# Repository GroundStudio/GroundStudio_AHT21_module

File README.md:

GroundStudio AHT21 module
====================================

Get it from [ardushop.ro](https://ardushop.ro/ro/home/2510-modul-senzor-umiditate-si-temperatura-aht21-groundstudio.html)

Explore all the GroundStudio products at [GroundStudio.ro](https://groundstudio.ro/)

Description
-------------------
Temperature and humidity sensor module based on AHT21 chip.

Contents
-------------------

* [/Documentation](https://github.com/GroundStudio/GroundStudio_AHT21_module/tree/main/Documentation) -- Contains documentation written during creation of this repository, with readme.md index of its own!
* [/Firmware](https://github.com/GroundStudio/GroundStudio_AHT21_module/tree/main/Firmware) -- Firmware (bootloaders, etc)
* [/Hardware](https://github.com/GroundStudio/GroundStudio_AHT21_module/tree/main/Hardware) -- Schematics, layout.
* [/Libraries](https://github.com/GroundStudio/GroundStudio_AHT21_module/tree/main/Libraries) -- Arduino/CircuitPython libraries. 
* [/Tools](https://github.com/GroundStudio/GroundStudio_AHT21_module/tree/main) -- Tools needed for compiling, uploading bootloader, etc.

Versions
-------------------
*(Not all tags shown)*
* [V0.0.1] Initial version

License
-------------------

This is released under the [Attribution-ShareAlike 4.0 International (CC BY-SA 4.0)](https://creativecommons.org/licenses/by-sa/4.0/) license. 
**You are welcome to use this for commercial purposes.**

Please consider contributing back to this project or others to help the open-source hardware community continue to thrive and grow! 

Certifications:

[Open Source Hardware Association](https://certification.oshwa.org/ro000019.html)   
   
[
](https://certification.oshwa.org/ro000019.html)

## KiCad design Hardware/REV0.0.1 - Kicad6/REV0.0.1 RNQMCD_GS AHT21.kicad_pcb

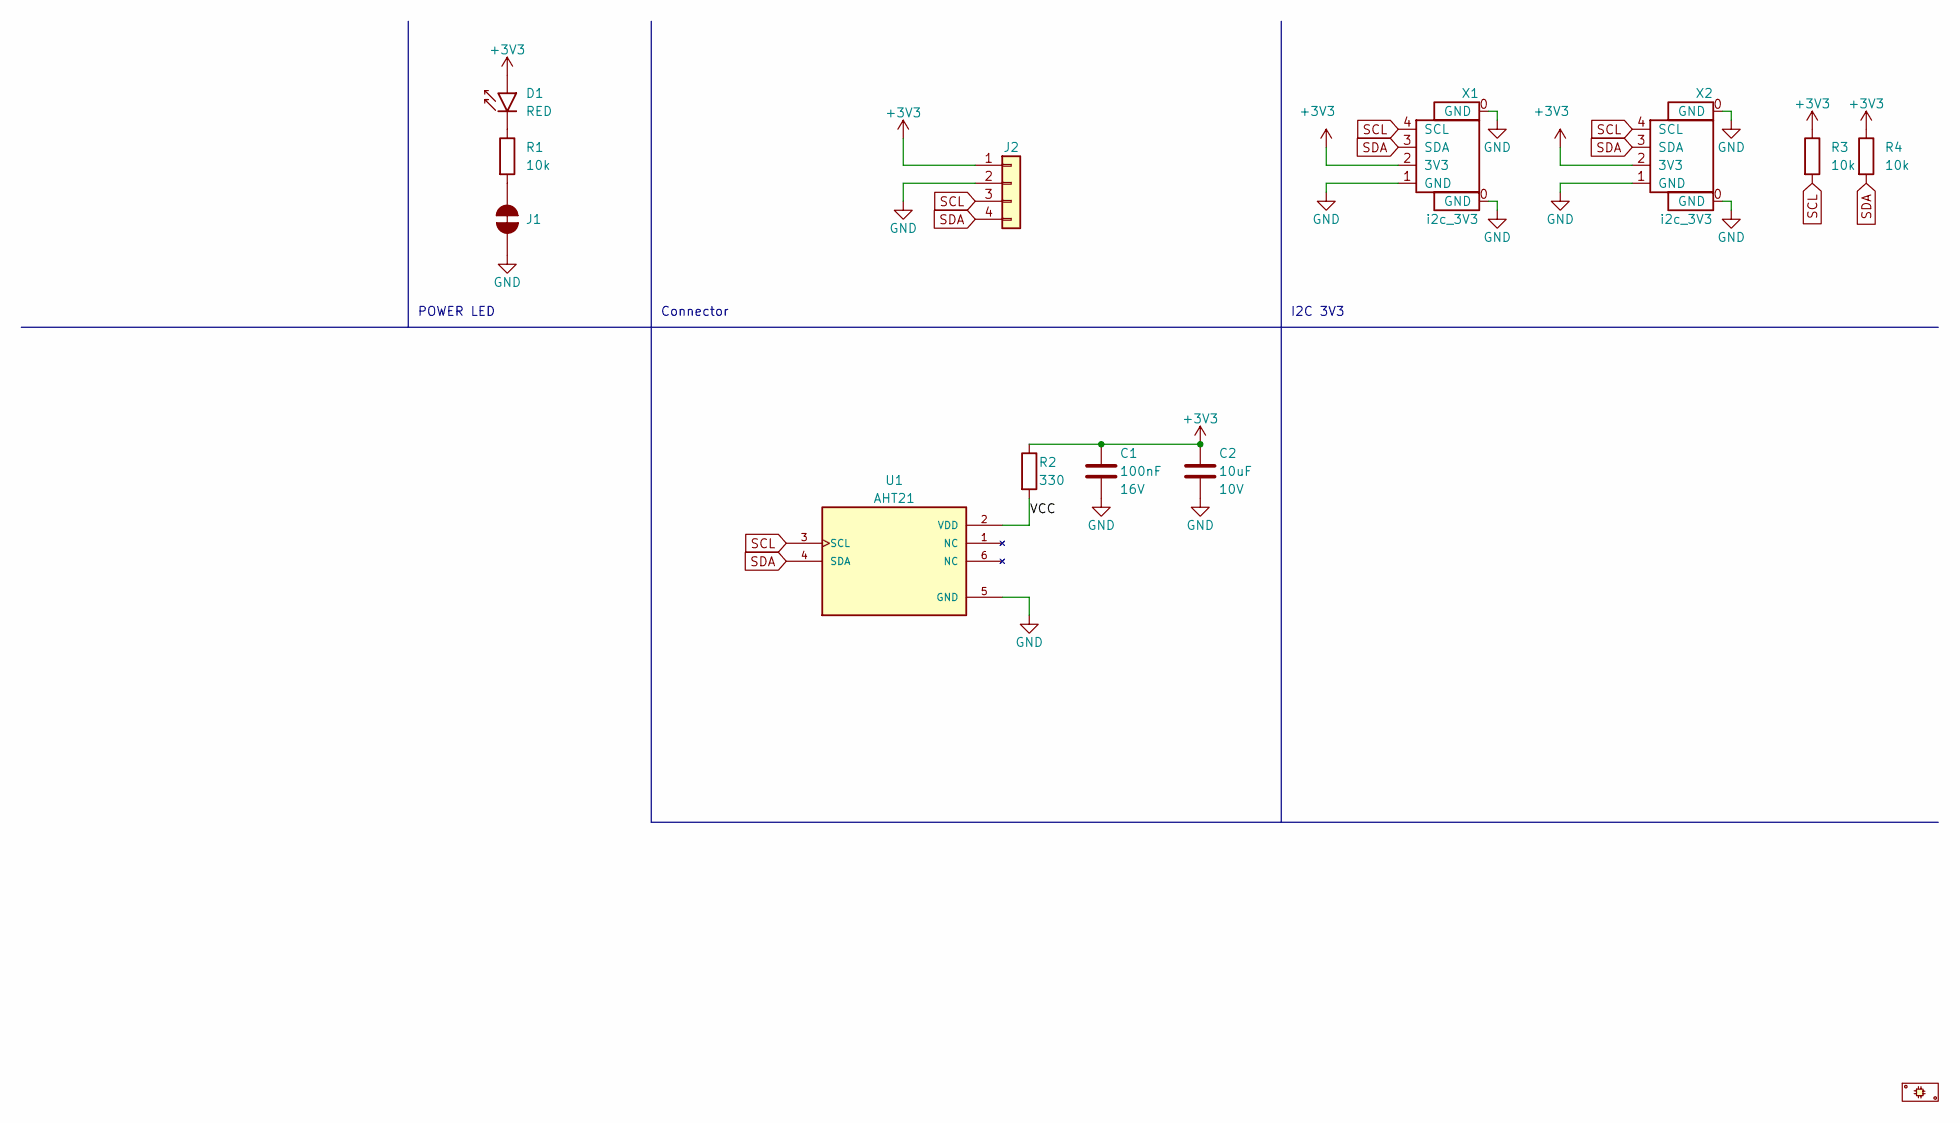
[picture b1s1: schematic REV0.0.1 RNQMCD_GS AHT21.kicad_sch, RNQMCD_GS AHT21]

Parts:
C1: C_0402_100nF_16V; C_0402_alt; Rated voltage 16V; MPN 0402B104K160CT; LCSC C83056
C2: C_0402_10uF_10V; C_0402_alt; Rated voltage 10V; MPN LDK105CBJ106MVLF; LCSC C386033
D1: LED_0402_RED; LED_0402_alt; MPN TZ-P2-0402RTIA1-0.45T; LCSC C779449
J1: SolderJumper_NC
J2: PinHeader_1x04_P2.54_V_M; PinHeader_1x04_P2.54mm_Vertical_Male; MPN MTP125-1104S1; LCSC C358686
P1: PCB; MPN RNQMCD_GS_PCB
R1, R3, R4: R_0402_10k; R_0402_alt; MPN 0402WGJ0103TCE; LCSC C25531
R2: R_0402_330; R_0402_alt; MPN 0402WGF3300TCE; LCSC C25104
U1: AHT21; AHT; MPN AHT21; LCSC C2827328
X1, X2: i2c_3V3; SH__1x04_P1.00mm_Horizontal; MPN C145956; LCSC C145956

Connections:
+3V3: C1.2, C2.1, D1.2 (A), J2.1, R2.1, R3.1, R4.1, X1.2 (3V3), X2.2 (3V3)
/VCC: R2.2, U1.2 (VDD)
GND: C1.1, C2.2, J1.2, J2.2, U1.5 (GND), X1.0 (GND), X1.1 (GND), X2.0 (GND), X2.1 (GND)
unnamed: D1.1 (K), R1.1
unnamed: J1.1, R1.2
SCL: J2.3, R3.2, U1.3 (SCL), X1.4 (SCL), X2.4 (SCL)
SDA: J2.4, R4.2, U1.4 (SDA), X1.3 (SDA), X2.3 (SDA)

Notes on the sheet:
Connector
POWER LED
I2C 3V3

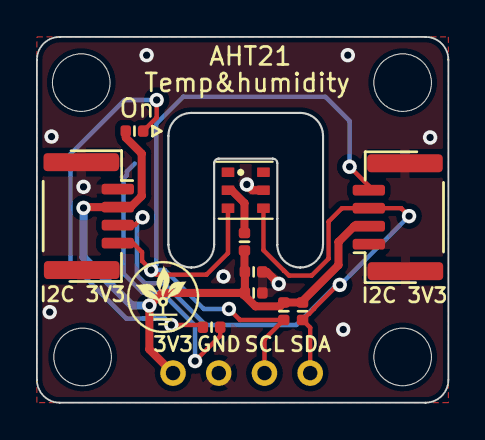
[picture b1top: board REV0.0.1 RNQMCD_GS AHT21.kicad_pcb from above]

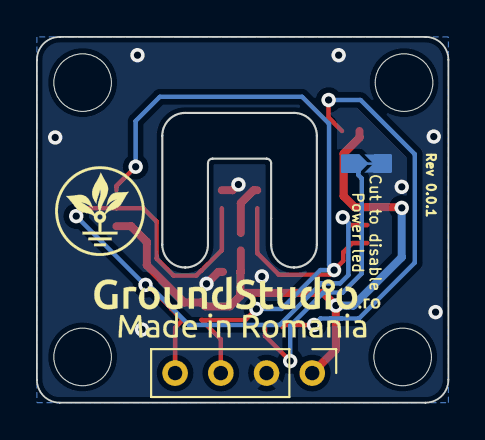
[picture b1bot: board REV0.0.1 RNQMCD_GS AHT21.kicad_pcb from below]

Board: 2 copper layers, 22.8 x 20.3 mm, 12 parts (2 on the bottom side), 7 nets.

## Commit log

2023-10-24 - first commit
2023-10-25 - added datasheet
